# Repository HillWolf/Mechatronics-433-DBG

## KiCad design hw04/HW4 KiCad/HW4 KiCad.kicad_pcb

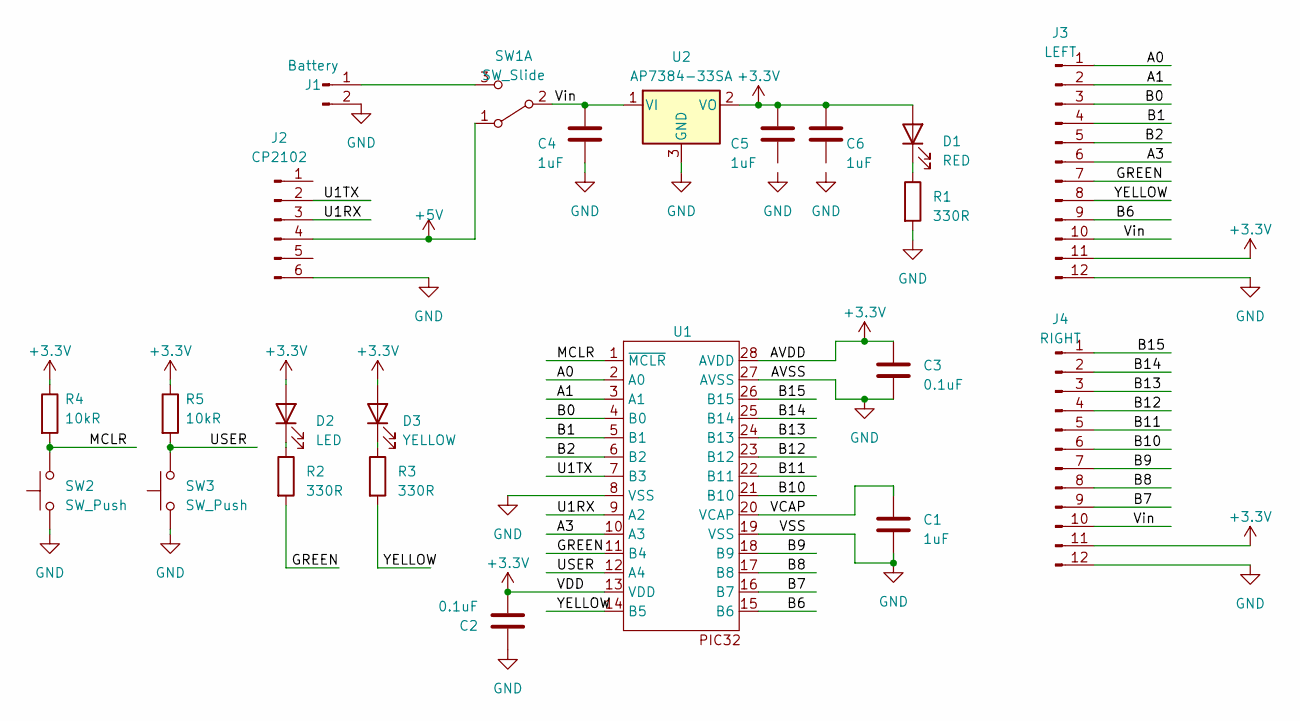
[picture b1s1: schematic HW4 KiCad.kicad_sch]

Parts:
C1, C4, C5, C6: 1uF; C_Disc_D5.1mm_W3.2mm_P5.00mm
C2, C3: 0.1uF; C_Disc_D3.4mm_W2.1mm_P2.50mm
D1: RED; LED_D3.0mm
D2: LED; LED_D3.0mm
D3: YELLOW; LED_D3.0mm
J1: Battery; PinSocket_1x02_P2.54mm_Vertical
J2: CP2102; PinSocket_1x06_P2.54mm_Vertical
J3: LEFT; PinSocket_1x12_P2.54mm_Vertical
J4: RIGHT; PinSocket_1x12_P2.54mm_Vertical
R1, R2, R3: 330R; R_Axial_DIN0207_L6.3mm_D2.5mm_P7.62mm_Horizontal
R4, R5: 10kR; R_Axial_DIN0207_L6.3mm_D2.5mm_P7.62mm_Horizontal
SW1: SW_Slide; slideswpic
SW2, SW3: SW_Push; pushbutton
U1: DIP-28_W7.62mm_Socket
U2: AP7384-33SA; TO-92L_Inline

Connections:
+3.3V: C2.2, C3.1, C5.2, C6.2, D1.2 (A), D2.2 (A), D3.2 (A), J3.11, J4.11, R4.1, R5.1, U1.13 (VDD), U1.28 (AVDD), U2.2 (VO)
+5V: J2.4, SW1.1 (A)
/A0: J3.1, U1.2 (A0)
/A1: J3.2, U1.3 (A1)
/A3: J3.6, U1.10 (A3)
/B0: J3.3, U1.4 (B0)
/B1: J3.4, U1.5 (B1)
/B2: J3.5, U1.6 (B2)
/B6: J3.9, U1.15 (B6)
/B7: J4.9, U1.16 (B7)
/B8: J4.8, U1.17 (B8)
/B9: J4.7, U1.18 (B9)
/B10: J4.6, U1.21 (B10)
/B11: J4.5, U1.22 (B11)
/B12: J4.4, U1.23 (B12)
/B13: J4.3, U1.24 (B13)
/B14: J4.2, U1.25 (B14)
/B15: J4.1, U1.26 (B15)
/GREEN: J3.7, R2.2, U1.11 (B4)
/MCLR: R4.2, SW2.2, U1.1 (~MCLR)
/U1RX: J2.3, U1.9 (A2)
/U1TX: J2.2, U1.7 (B3)
/USER: R5.2, SW3.2, U1.12 (A4)
/VCAP: C1.1, U1.20 (VCAP)
/Vin: C4.2, J3.10, J4.10, SW1.2 (B), U2.1 (VI)
/YELLOW: J3.8, R3.2, U1.14 (B5)
GND: C1.2, C2.1, C3.2, C4.1, J1.2, J2.6, J3.12, J4.12, R1.2, SW2.1, SW3.1, U1.8 (VSS), U1.19 (VSS), U1.27 (AVSS), U2.3 (GND)
unnamed: D1.1 (K), R1.1
unnamed: D2.1 (K), R2.1
unnamed: D3.1 (K), R3.1
unnamed: J1.1, SW1.3 (C)

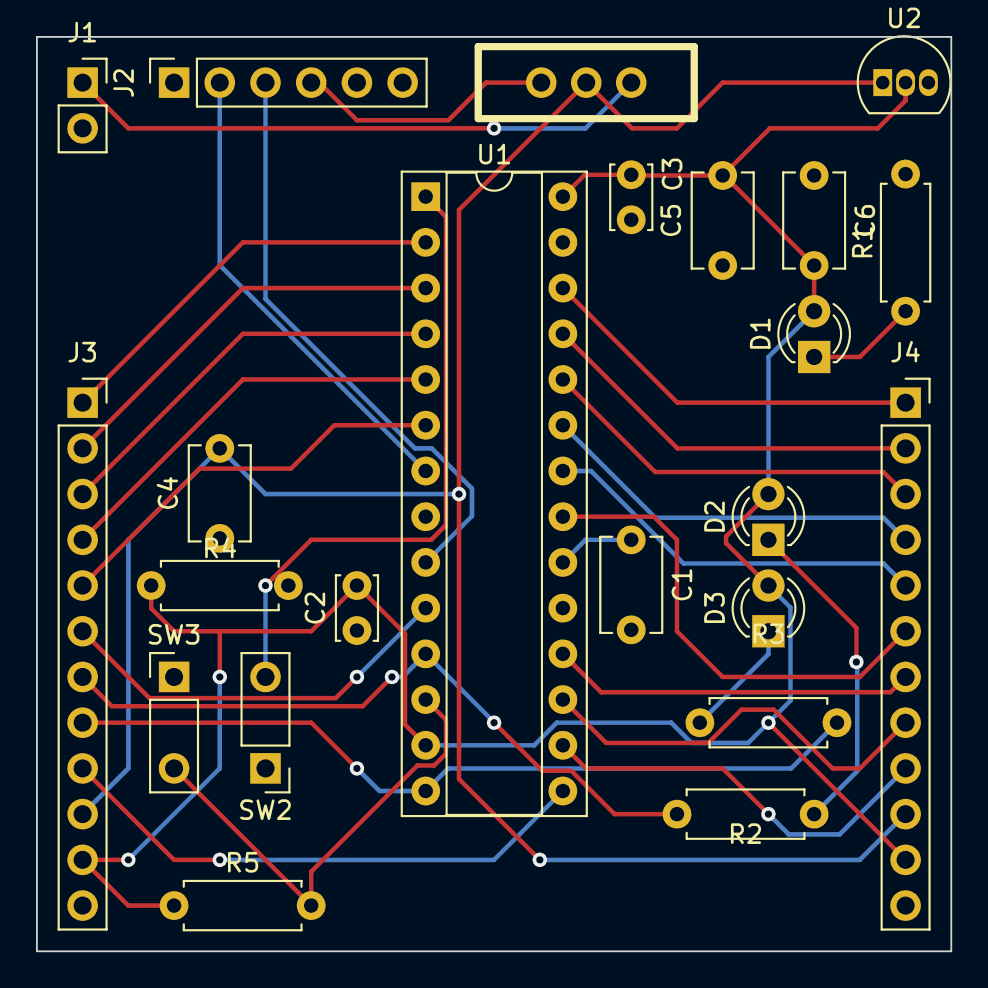
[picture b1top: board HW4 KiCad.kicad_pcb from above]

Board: 2 copper layers, 50.8 x 50.8 mm, 23 parts (0 on the bottom side), 31 nets.

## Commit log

2023-06-07 hw2 submission
2023-06-07 hw3 submission
2023-06-07 hw5 submission
2023-06-07 hw6 submission
2023-06-10 hw7 submission
2023-06-10 hw8 submission
2023-06-10 hw9 submission
2023-06-10 hw10 submission
2023-06-10 rename
2023-06-10 hw 11 submission
2023-06-10 hw12 submission
2023-06-10 hw14 submission
2023-06-10 hw15 submission
2023-06-11 hw4 submission
